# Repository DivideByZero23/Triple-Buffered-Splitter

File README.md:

# Triple-Buffered-Splitter
Buffered splitter for 1/4" mono signals.

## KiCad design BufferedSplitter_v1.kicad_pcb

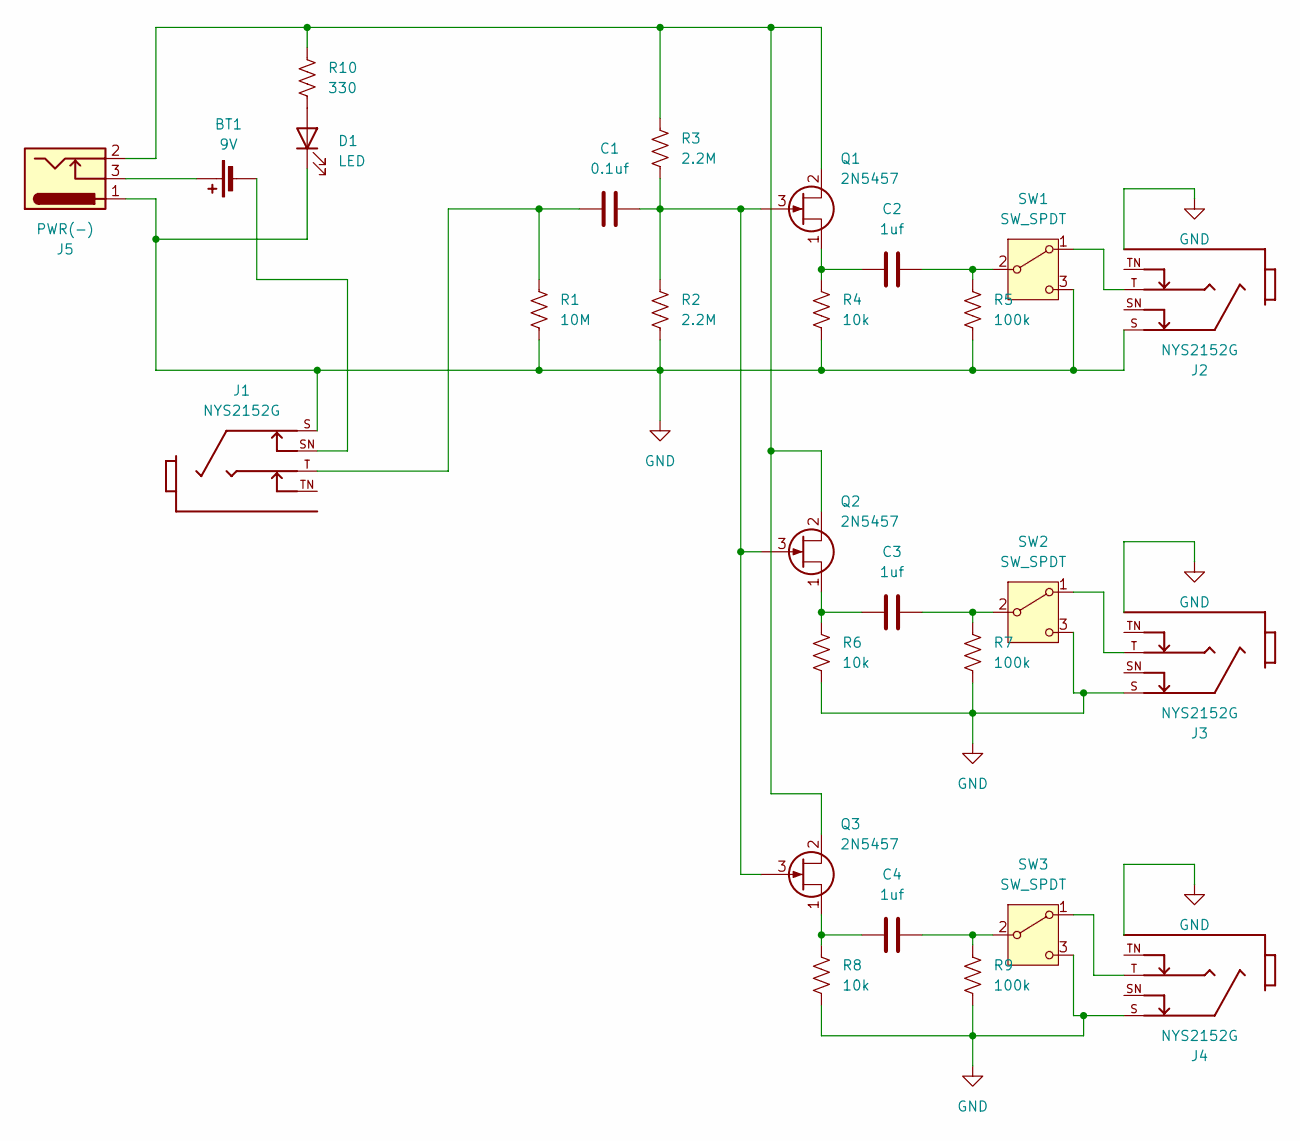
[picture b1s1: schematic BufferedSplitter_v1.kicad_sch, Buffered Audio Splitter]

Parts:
BT1: 9V; PinHeader_1x02_P2.54mm_Vertical
C1: 0.1uf; C_1206_3216Metric_Pad1.33x1.80mm_HandSolder
C2, C3, C4: 1uf; C_1206_3216Metric_Pad1.33x1.80mm_HandSolder
D1: LED; LED_1206_3216Metric_Pad1.42x1.75mm_HandSolder
J1, J2, J3, J4: NYS2152G; REAN_NYS2152G; PARTREV 2015.06.01
J5: PWR(-); PinHeader_1x03_P2.54mm_Vertical
Q1, Q2, Q3: 2N5457; SOT-23-3
R1: 10M; R_1206_3216Metric_Pad1.30x1.75mm_HandSolder
R2, R3: 2.2M; R_1206_3216Metric_Pad1.30x1.75mm_HandSolder
R4, R6, R8: 10k; R_1206_3216Metric_Pad1.30x1.75mm_HandSolder
R5, R7, R9: 100k; R_1206_3216Metric_Pad1.30x1.75mm_HandSolder
R10: 330; R_1206_3216Metric_Pad1.30x1.75mm_HandSolder
SW1, SW2, SW3: SW_SPDT; PushButton Switch

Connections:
GND: D1.1 (K), J1.S, J2.S, J3.S, J4.S, J5.1, R1.2, R2.2, R4.2, R5.2, R6.2, R7.2, R8.2, R9.2, SW1.3 (C), SW2.3 (C), SW3.3 (C)
unnamed: BT1.1 (+), J5.3
unnamed: BT1.2 (-), J1.SN
unnamed: C1.2, J1.T, R1.1
unnamed: D1.2 (A), R10.2
unnamed: J5.2, Q1.2 (D), Q2.2 (D), Q3.2 (D), R3.1, R10.1
unnamed: C1.1, Q1.3 (G), Q2.3 (G), Q3.3 (G), R2.1, R3.2
unnamed: C2.2, Q1.1 (S), R4.1
unnamed: C3.2, Q2.1 (S), R6.1
unnamed: C4.2, Q3.1 (S), R8.1
unnamed: J2.T, SW1.1 (A)
unnamed: C2.1, R5.1, SW1.2 (B)
unnamed: J3.T, SW2.1 (A)
unnamed: C3.1, R7.1, SW2.2 (B)
unnamed: J4.T, SW3.1 (A)
unnamed: C4.1, R9.1, SW3.2 (B)

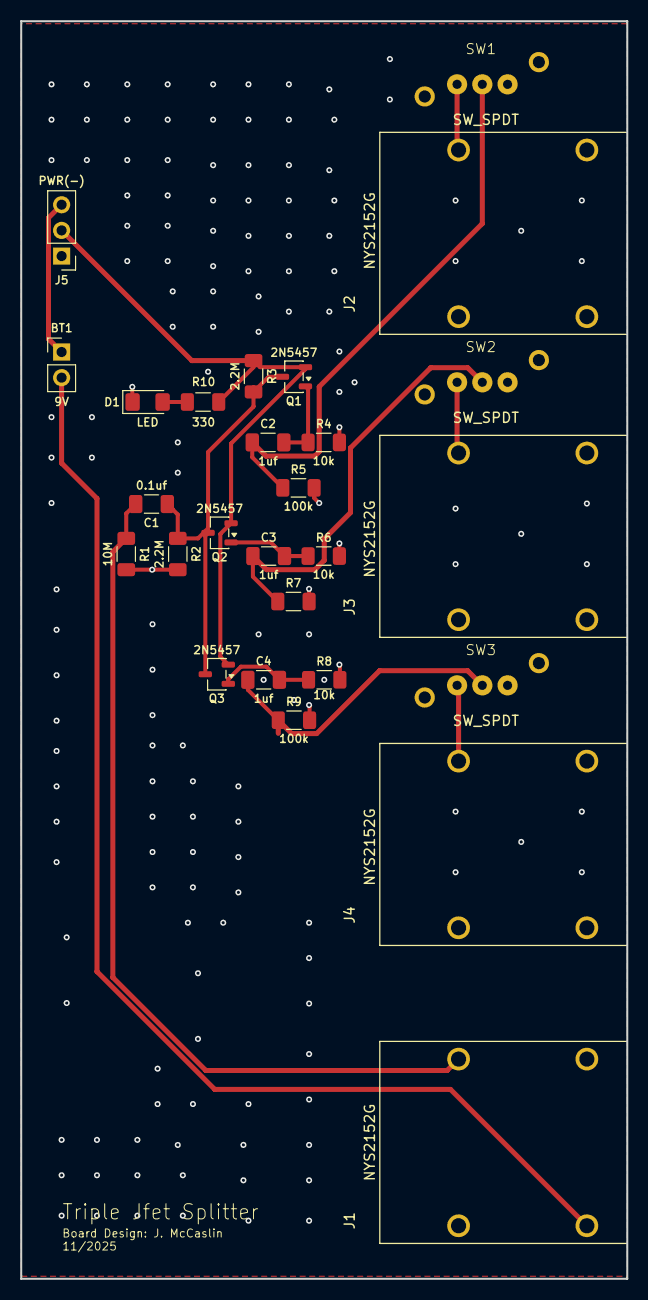
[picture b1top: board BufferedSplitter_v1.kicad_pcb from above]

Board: 2 copper layers, 60.0 x 124.5 mm, 27 parts (0 on the bottom side), 16 nets.

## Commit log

2025-11-27 Actual initial commit.
2025-11-27 Rendered PCBWay files.
